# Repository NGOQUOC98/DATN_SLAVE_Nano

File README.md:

# DATN_SLAVE_Nano
## Hardware

### Schematics

### 3D

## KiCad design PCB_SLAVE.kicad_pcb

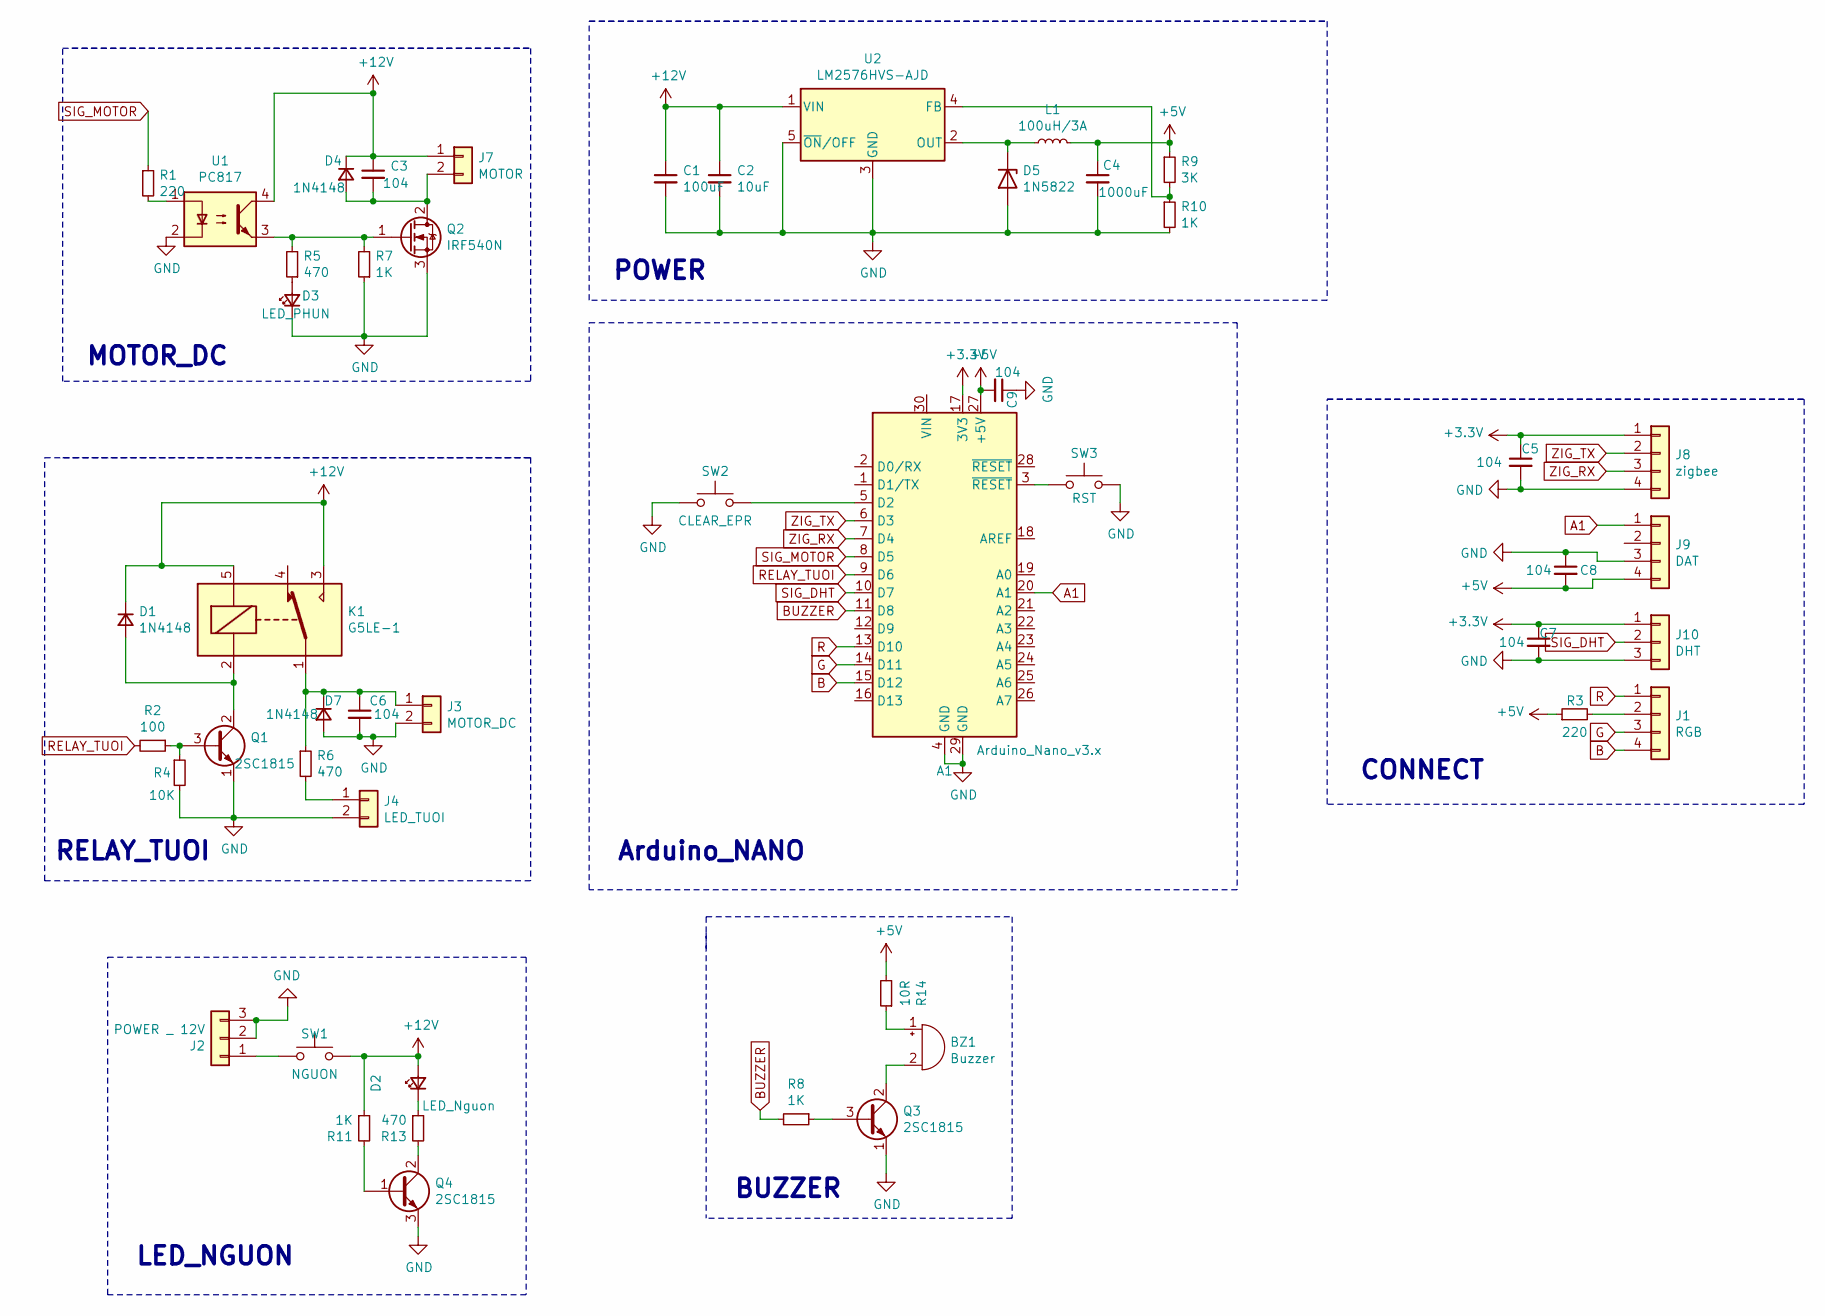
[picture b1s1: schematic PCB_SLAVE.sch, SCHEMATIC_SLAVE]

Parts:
A1: Arduino_Nano_v3.x; Arduino_Nano
BZ1: Buzzer; MagneticBuzzer_ProSignal_ABT-410-RC
C1: 100uF; CP_Radial_D5.0mm_P2.50mm
C2: 10uF; CP_Radial_D5.0mm_P2.00mm
C3, C5, C6, C7, C8, C9: 104; C_Disc_D3.0mm_W1.6mm_P2.50mm
C4: 1000uF; CP_Radial_D8.0mm_P3.80mm
D1: 1N4148; D_DO-41_SOD81_P10.16mm_Horizontal
D2: LED_Nguon; LED_D3.0mm
D3: LED_PHUN; LED_D3.0mm
D4, D7: 1N4148; D_DO-34_SOD68_P2.54mm_Vertical_AnodeUp
D5: 1N5822; D_5W_P10.16mm_Horizontal
J1: RGB; PinHeader_1x04_P1.00mm_Vertical
J2: POWER _ 12V; jack_DC
J3: MOTOR_DC; PinHeader_1x02_P2.54mm_Vertical
J4: LED_TUOI; PinHeader_1x02_P2.54mm_Vertical
J7: MOTOR; PinHeader_1x02_P2.54mm_Vertical
J8: zigbee; PinHeader_1x04_P2.54mm_Vertical
J9: DAT; PinHeader_1x04_P2.54mm_Vertical
J10: DHT; PinHeader_1x03_P2.54mm_Vertical
K1: G5LE-1; Relay_SPDT_Omron-G5LE-1
L1: 100uH/3A; L_Axial_L7.0mm_D3.3mm_P10.16mm_Horizontal_Fastron_MICC
Q1, Q3, Q4: 2SC1815; PinHeader_1x03_P1.27mm_Vertical
Q2: IRF540N; TO-220-3_Vertical
R1: 220; R_Axial_DIN0309_L9.0mm_D3.2mm_P15.24mm_Horizontal
R2: 100; R_Axial_DIN0309_L9.0mm_D3.2mm_P15.24mm_Horizontal
R3: 220; R_Axial_DIN0207_L6.3mm_D2.5mm_P10.16mm_Horizontal
R4: 10K; R_Axial_DIN0309_L9.0mm_D3.2mm_P15.24mm_Horizontal
R5, R6: 470; R_Axial_DIN0207_L6.3mm_D2.5mm_P10.16mm_Horizontal
R7: 1K; R_Axial_DIN0207_L6.3mm_D2.5mm_P10.16mm_Horizontal
R8, R10, R11: 1K; R_Axial_DIN0309_L9.0mm_D3.2mm_P15.24mm_Horizontal
R9: 3K; R_Axial_DIN0309_L9.0mm_D3.2mm_P15.24mm_Horizontal
R13: 470; R_Axial_DIN0309_L9.0mm_D3.2mm_P15.24mm_Horizontal
R14: 10R; R_Axial_DIN0309_L9.0mm_D3.2mm_P15.24mm_Horizontal
SW1: NGUON; PinHeader_1x02_P2.54mm_Vertical
SW2: CLEAR_EPR; PinHeader_1x02_P2.54mm_Vertical
SW3: RST; PinHeader_1x02_P2.54mm_Vertical
U1: PC817; DIP-4_W7.62mm
U2: LM2576HVS-AJD; TO-220-5_Vertical

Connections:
+12V: C1.1, C2.1, C3.1, D1.1 (K), D2.2 (A), D4.1 (K), J7.1, K1.3, K1.5, R11.1, SW1.2, U1.4, U2.1 (VIN)
A1: A1.20 (A1), J9.1
B: A1.15 (D12), J1.4
BUZZER: A1.11 (D8), R8.2
G: A1.14 (D11), J1.3
GND: A1.4 (GND), A1.29 (GND), C1.2, C2.2, C4.2, C5.2, C6.2, C7.2, C8.1, C9.1, D3.1 (K), D5.2 (A), D7.2 (A), J2.2, J2.3, J3.2, J4.2, J8.4, J9.3, J10.3, Q1.1 (E), Q2.3 (S), Q3.1 (E), Q4.3 (E), R4.2, R7.1, R10.2, SW2.1, SW3.2, U1.2, U2.3 (GND), U2.5 (~ON~/OFF)
unnamed: A1.3 (~RESET), SW3.1
unnamed: A1.5 (D2), SW2.2
unnamed: BZ1.1 (-), R14.1
unnamed: BZ1.2 (+), Q3.2 (C)
unnamed: C3.2, D4.2 (A), J7.2, Q2.2 (D)
unnamed: C6.1, D7.1 (K), J3.1, K1.1, R6.1
unnamed: D1.2 (A), K1.2, Q1.2 (C)
unnamed: D2.1 (K), R13.1
unnamed: D3.2 (A), R5.1
unnamed: D5.1 (K), L1.1, U2.2 (OUT)
unnamed: J1.2, R3.2
unnamed: J2.1, SW1.1
unnamed: J4.1, R6.2
unnamed: Q1.3 (B), R2.1, R4.1
unnamed: Q2.1 (G), R5.2, R7.2, U1.3
unnamed: Q3.3 (B), R8.1
unnamed: Q4.1 (B), R11.2
unnamed: Q4.2 (C), R13.2
unnamed: R1.2, U1.1
unnamed: R9.2, R10.1, U2.4 (FB)
R: A1.13 (D10), J1.1
RELAY_TUOI: A1.9 (D6), R2.2
SIG_DHT: A1.10 (D7), J10.2
SIG_MOTOR: A1.8 (D5), R1.1
ZIG_RX: A1.7 (D4), J8.3
ZIG_TX: A1.6 (D3), J8.2

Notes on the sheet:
Arduino_NANO
CONNECT
BUZZER
POWER
RELAY_TUOI
MOTOR_DC
LED_NGUON

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
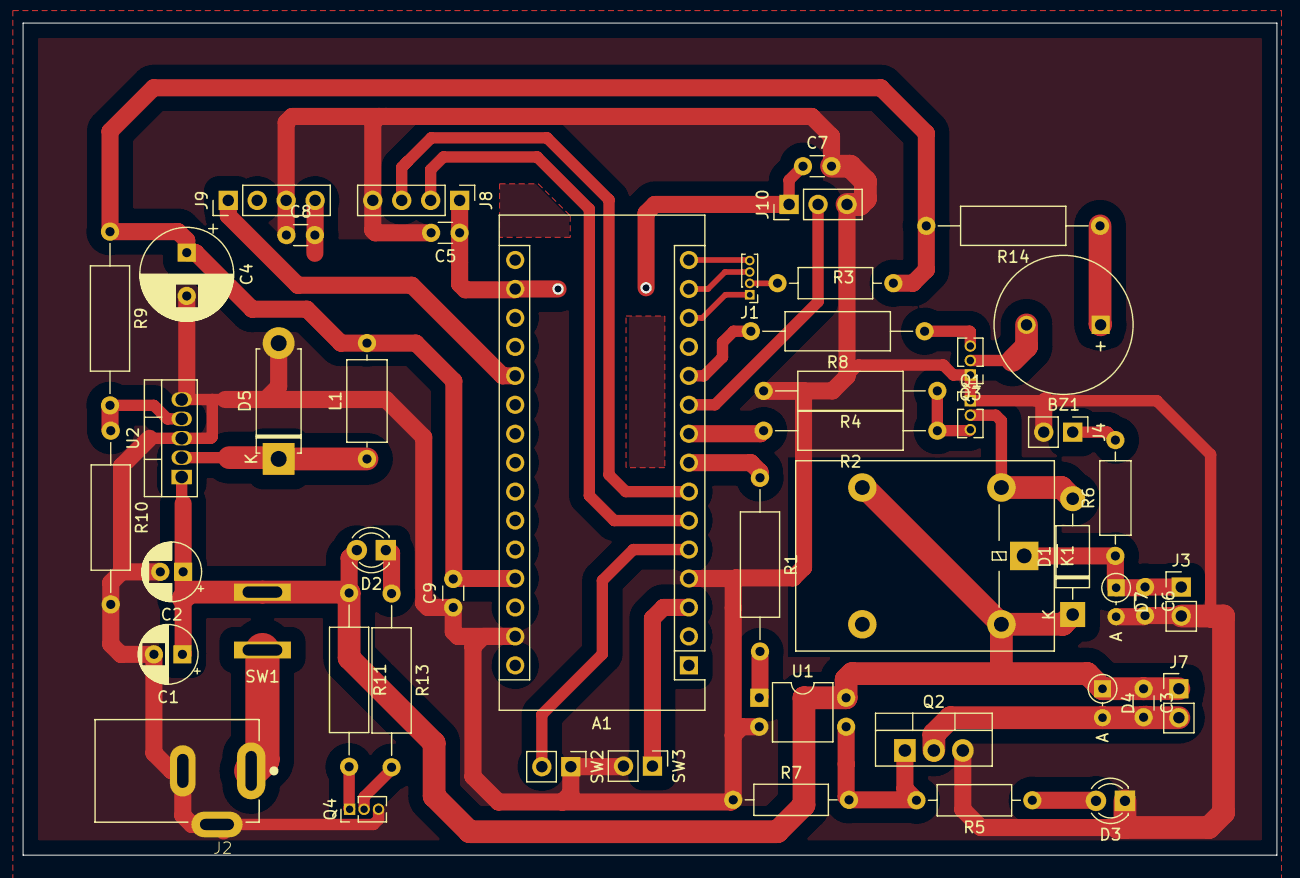
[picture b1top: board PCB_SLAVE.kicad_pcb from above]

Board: 2 copper layers, 110.0 x 73.0 mm, 49 parts (0 on the bottom side), 34 nets.

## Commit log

2020-12-14 add fiel DATN
2020-12-18 edit
2020-12-25 add file
